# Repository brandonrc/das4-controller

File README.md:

# das4-controller

An open-source replacement controller board for the **Das Keyboard 4 Professional**:
same outline, same holes, same connectors, but with an **RP2350B** you can flash
with your own firmware (pico-sdk today, KMK/CircuitPython, QMK once it supports the RP2350B). It keeps the two USB-A ports (as a USB 2.0
hub), the volume knob, the NUM/CAPS/SCROLL LEDs (now RGB, any colour) and the five buttons. Every
button gets its own GPIO, so you can make them do whatever you like.

> **Status: ready to order after a final 1:1 fit print.** Routed, DRC clean (0 unconnected, 0 real
> violations), with independent circuit and layout reviews, a check against Raspberry Pi's RP2350
> design guide, and a firmware build for this pinout. See [docs/plan.md](docs/plan.md).

| Top | Bottom |
|---|---|
|  |  |

## Docs

- [Plan and status](docs/plan.md): what's done, next steps, bring-up and firmware plan
- [Design notes](docs/design.md): architecture, circuit blocks, GPIO map, ordering, open questions
- [Bill of materials](docs/bom.md): every part with its LCSC number and live JLCPCB stock
- [Measurements](docs/measurements.md): every dimension, where it came from and how sure we are
- [Fit-check PDF](docs/fit-check-1to1.pdf): print at 100% and lay the original board on it
- Reviews: [circuit](docs/review-2026-09-25.md), [layout 1](docs/review-layout-2026-09-25.md),
  [layout 2](docs/review-layout-2-2026-09-25.md), [RPi design guide](docs/rpi-guide-check-2026-09-26.md),
  [firmware](docs/firmware-check-2026-09-26.md)
- [AGENTS.md](AGENTS.md): how the pipeline works and what to watch out for (for AI agents and humans)

## Layout

```
hardware/
  circuit/das4.py                          the circuit (SKiDL)
  das4-controller.net                      netlist generated from it
  das4-controller.kicad_pro / .kicad_pcb   KiCad 10 project (board generated from the netlist)
  lib/jlc.*                                JLCPCB part symbols, footprints and 3D models (easyeda2kicad)
  lib/das4.pretty                          our own footprints (J4 flex solder pads)
  scripts/gen_board.py                     outline, measured positions, placement, silkscreen
  scripts/critical.py                      hand-drawn critical nets + keep-outs (RP2350 regulator, USB pair, crystal...)
  scripts/route.py, route_best.py          autorouting (Freerouting) + cleanup + GND stitching, best of 6 runs
  scripts/pretest.py, check_layout.py      pre-route DRC of the hand layout; post-route checks
  scripts/jlc_fab.py                       JLCPCB gerber zip, BOM and CPL
  scripts/jlc.py                           search JLCPCB's parts library (no login)
  scripts/bom.py                           docs/bom.md with live stock
docs/                                      notes, plan, reviews, renders, fit-check print
firmware/bringup/                          pico-sdk + TinyUSB bring-up firmware for this pinout
```

## Building

The tools come from the KiBot/KiCad container
[`ghcr.io/inti-cmnb/kicad10_auto_full`](https://github.com/INTI-CMNB/kicad_auto),
which is also what CI runs.

```sh
# one-time: create the container
distrobox create --name pcb --image ghcr.io/inti-cmnb/kicad10_auto_full:1.9.1-1_k10.0.5_d13.2_b4.2.4LTS

distrobox enter pcb -- make pretest       # quick DRC of just the hand layout (run before routing)
distrobox enter pcb -- make board route   # circuit -> netlist -> placed board -> autorouted (~25 min)
distrobox enter pcb -- make check         # post-route checks DRC can't do
distrobox enter pcb -- make docs drc fab  # renders, fit-check PDF, DRC, JLCPCB files (don't rebuild the board)
distrobox enter pcb -- make bom      # refresh docs/bom.md with live JLCPCB stock
```

Or use Docker directly:
`docker run --rm -v $PWD:/w -w /w ghcr.io/inti-cmnb/kicad10_auto_full:1.9.1-1_k10.0.5_d13.2_b4.2.4LTS make`.

Open `hardware/das4-controller.kicad_pro` in KiCad 10 to look around.

**Note:** the board file is *generated*: `make board` rebuilds it (unrouted)
from the circuit and `gen_board.py`, and `make route` routes it. Edit those,
not the .kicad_pcb, or your changes get overwritten.

## Ordering (JLCPCB)

```sh
distrobox enter pcb -- make fab     # -> build/jlcpcb/: gerber zip, bom.csv, cpl.csv
```

1. On jlcpcb.com upload the gerber zip. Pick **4 layers**, 1.6 mm, and the **JLC04161H-7628** stackup with impedance control.
2. Enable **PCB Assembly** (top side), upload `bom.csv` and `cpl.csv`, and check the placement preview:
   rotations, and L1's white dot on the +1V1 pad next to C165 (details in [docs/design.md](docs/design.md#ordering-at-jlcpcb)).
3. Order the "You solder" parts in [docs/bom.md](docs/bom.md) from LCSC (they can ship together).

`make fab` names the zip `...-UNROUTED-quote-only` if the board has no traces yet.

## License

MIT, see [LICENSE](LICENSE). Not affiliated with Das Keyboard / Metadot.

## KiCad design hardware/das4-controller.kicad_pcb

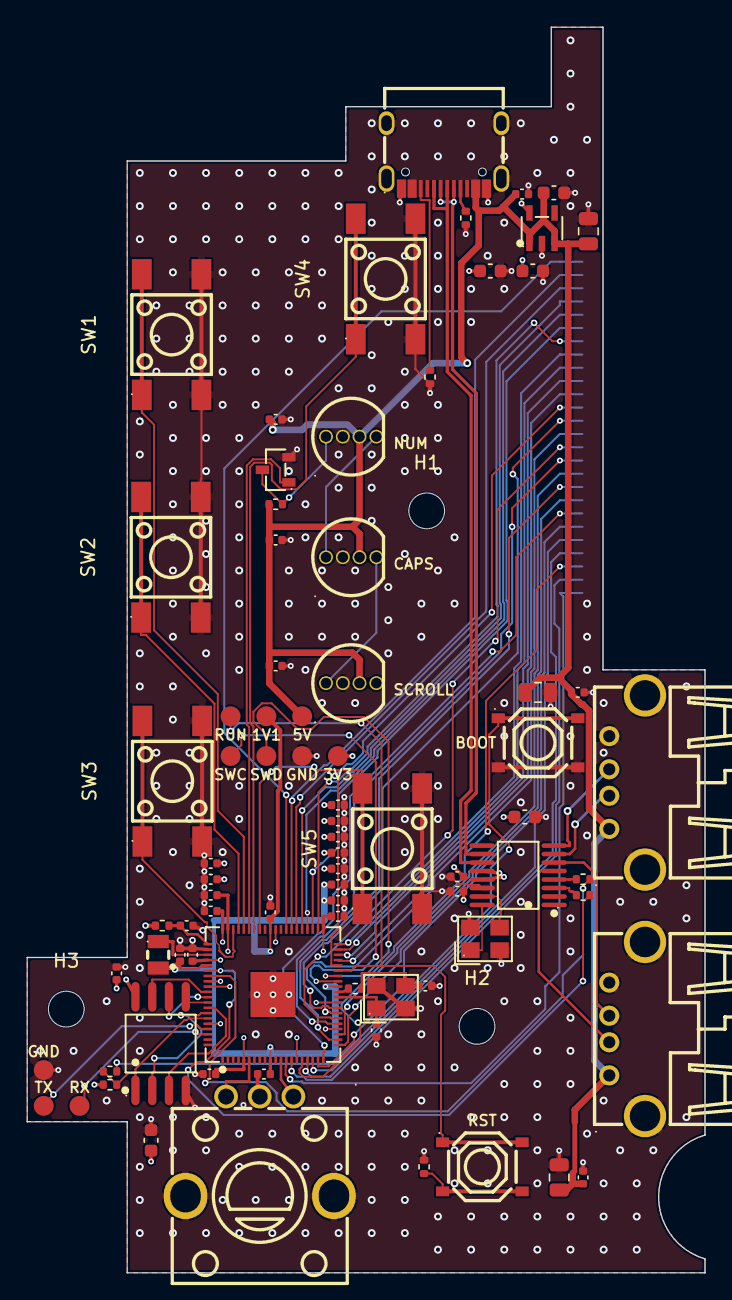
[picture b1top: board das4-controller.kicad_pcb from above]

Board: 4 copper layers, 51.1 x 94.0 mm, 83 parts (1 on the bottom side), 73 nets.

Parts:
C1, C9, C11: 22u; C_0805_2012Metric
C2, C7, C10, C12, C35, C36, C37, C105, C110, C115, C124, C129, C132, C141, C150, C151, C159, C160, C168, C169, C176, C300: 100n; C_0402_1005Metric
C3, C4, C5, C8, C190: 10u; C_0603_1608Metric
C6: 1u; C_0402_1005Metric
C161, C164, C165, C166: 4.7u; C_0402_1005Metric
C230, C231: 15p; C_0402_1005Metric
D1: NUM (RGB); LED-TH_4P-BD5.8-P1.27_WS2812D-F5-12MA-C1
D2: CAPS (RGB); LED-TH_4P-BD5.8-P1.27_WS2812D-F5-12MA-C1
D3: SCROLL (RGB); LED-TH_4P-BD5.8-P1.27_WS2812D-F5-12MA-C1
ENC1: EC12E24204A2; SW-TH_EC12E24204A2
H1, H2, H3: MountingHole_2.7mm_M2.5
J1: USB-C; USB-C_SMD-TYPE-C-31-M-12_1
J2: USB-A 1; USB-A-TH_AF-WJDG
J3: USB-A 2; USB-A-TH_AF-WJDG
J4: Key matrix flex; FPC_Solder_1x26_P1.00mm
L1: 3.3uH; IND-SMD_L2.0-W1.6_AOTA-B201610S3R3-101-T
Q1: 2N7002; SOT-23-3_L2.9-W1.3-P1.90-LS2.4-BR
R1, R2: 5.1k; R_0402_1005Metric
R10, R231, R302, R303: 1k; R_0402_1005Metric
R161: 33; R_0402_1005Metric
R266, R267: 22; R_0402_1005Metric
R301: 10k; R_0402_1005Metric
SW1: Button 1; SW-SMD_4P-L6.0-W6.0-P4.50-LS9.0_H5.0
SW2: Button 2; SW-SMD_4P-L6.0-W6.0-P4.50-LS9.0_H5.0
SW3: Button 3; SW-SMD_4P-L6.0-W6.0-P4.50-LS9.0_H5.0
SW4: Button 4; SW-SMD_4P-L6.0-W6.0-P4.50-LS9.0_H5.0
SW5: Button 5; SW-SMD_4P-L6.0-W6.0-P4.50-LS9.0_H5.0
SW6: BOOTSEL; SW-SMD_4P-L5.1-W5.1-P3.70-LS6.5-TL_H1.5
SW7: RESET; SW-SMD_4P-L5.1-W5.1-P3.70-LS6.5-TL_H1.5
TP1, TP2, TP3, TP4, TP5, TP6, TP7, TP8, TP9, TP10: TestPoint; TestPoint_Pad_D1.5mm
U1: RP2350B; QFN-80_L10.0-W10.0-P0.40-TL-EP3.4
U2: CH334R; QSOP-16_L4.9-W3.9-P0.64-LS6.0-BL
U3: W25Q128JVS; SOIC-8_L5.3-W5.3-P1.27-LS8.0-BL
U4: ME6211C33M5G-N; SOT-23-5_L3.0-W1.7-P0.95-LS2.8-BL
Y1, Y2: 12MHz; CRYSTAL-SMD_4P-L3.2-W2.5-BL

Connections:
+1V1: C110.1, C132.1, C151.1, C165.1, C166.1, L1.2, TP6.1, U1.10, U1.32, U1.51, U1.65
+3V3: C4.1, C5.1, C6.1, C7.1, C8.1, C105.1, C115.1, C124.1, C129.1, C141.1, C150.1, C159.1, C160.1, C164.1, C168.1, C169.1, C176.1, C190.1, C300.1, R161.1, R301.1, TP4.1, U1.5, U1.15, U1.24, U1.29, U1.41, U1.50, U1.59, U1.60, U1.64, U1.68, U1.69, U1.76, U2.12, U2.13, U3.8, U4.5
+5V: C1.1, C2.1, C3.1, C9.1, C10.1, C11.1, C12.1, C35.1, C36.1, C37.1, D1.2, D2.2, D3.2, J1.A4B9, J2.1, J3.1, R10.1, TP7.1, U4.1, U4.3
BTN1: SW1.1, SW1.2, U1.56
BTN2: SW2.1, SW2.2, U1.57
BTN3: SW3.1, SW3.2, U1.58
BTN4: SW4.1, SW4.2, U1.54
BTN5: SW5.1, SW5.2, U1.53
ENC_A: ENC1.A, U1.12
ENC_B: ENC1.B, U1.6
GND: C1.2, C2.2, C3.2, C4.2, C5.2, C6.2, C7.2, C8.2, C9.2, C10.2, C11.2, C12.2, C35.2, C36.2, C37.2, C105.2, C110.2, C115.2, C124.2, C129.2, C132.2, C141.2, C150.2, C151.2, C159.2, C160.2, C161.2, C164.2, C165.2, C166.2, C168.2, C169.2, C176.2, C190.2, C230.2, C231.2, C300.2, D1.3, D2.3, D3.3, ENC1.C, ENC1.D, ENC1.E, J1.1, J1.2, J1.3, J1.4, J1.A1B12, J1.B1A12, J2.4, J2.5, J3.4, J3.5, Q1.2, R1.2, R2.2, R303.2, SW1.3, SW1.4, SW2.3, SW2.4, SW3.3, SW3.4, SW4.3, SW4.4, SW5.3, SW5.4, SW6.3, SW6.4, TP3.1, TP10.1, U1.62, U1.81, U2.14, U3.4, U4.2, Y1.2, Y1.4, Y2.2, Y2.4
KM1: J4.1, U1.48
KM2: J4.2, U1.47
KM3: J4.3, U1.46
KM4: J4.4, U1.45
KM5: J4.5, U1.44
KM6: J4.6, U1.43
KM7: J4.7, U1.42
KM8: J4.8, U1.40
KM9: J4.9, U1.39
KM10: J4.10, U1.38
KM11: J4.11, U1.37
KM12: J4.12, U1.36
KM13: J4.13, U1.28
KM14: J4.14, U1.27
KM15: J4.15, U1.26
KM16: J4.16, U1.25
KM17: J4.17, U1.23
KM18: J4.18, U1.22
KM19: J4.19, U1.21
KM20: J4.20, U1.20
KM21: J4.21, U1.19
KM22: J4.22, U1.18
KM23: J4.23, U1.17
KM24: J4.24, U1.16
KM25: J4.25, U1.14
KM26: J4.26, U1.13
LED_DATA_N: Q1.1, U1.55
LED_DIN1: D1.4, Q1.3, R10.2
LED_DIN2: D1.1, D2.4
LED_DIN3: D2.1, D3.4
unnamed: J1.A5, R1.1
unnamed: J1.B5, R2.1
unnamed: U2.16, Y2.1
unnamed: U2.15, Y2.3
unnamed: R231.1, U1.31
unnamed: R267.2, U1.67
unnamed: R266.2, U1.66
unnamed: TP1.1, U1.33
unnamed: TP2.1, U1.34
unnamed: TP8.1, U1.77
unnamed: TP9.1, U1.78
QSPI_SCLK: U1.71, U3.6
QSPI_SD0: U1.72, U3.5
QSPI_SD1: U1.74, U3.2
QSPI_SD2: U1.73, U3.3
QSPI_SD3: U1.70, U3.7
QSPI_SS: R301.2, R302.1, U1.75, U3.1
RUN: SW7.1, SW7.2, TP5.1, U1.35
RUN_BTN: R303.1, SW7.3, SW7.4
USB_A1_D+: J2.3, U2.8
USB_A1_D-: J2.2, U2.7
USB_A2_D+: J3.3, U2.6
USB_A2_D-: J3.2, U2.5
USB_BOOT: R302.2, SW6.1, SW6.2
USB_MCU_D+: R267.1, U2.4
USB_MCU_D-: R266.1, U2.3
USB_UP_D+: J1.A6, J1.B6, U2.11
USB_UP_D-: J1.A7, J1.B7, U2.10
VREG_AVDD: C161.1, R161.2, U1.61
VREG_LX: L1.1, U1.63
XIN: C230.1, U1.30, Y1.1
XOUT_XTAL: C231.1, R231.2, Y1.3

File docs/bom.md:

# Bill of materials

Generated by `hardware/scripts/bom.py` from the netlist, with live JLCPCB stock (re-run it before ordering).

- **JLCPCB assembles 58 parts**: 20 unique LCSC numbers, **6 Extended** (JLCPCB charges a loading fee per Extended part type, about $3 each), about **$7.24** per board
- **You solder 11 parts** (through-hole + 6x6 buttons), about **$1.65** per board from LCSC

## Assembled by JLCPCB

| Refs | Qty | Value | Part | LCSC | Type | Stock | Unit |
|---|---|---|---|---|---|---|---|
| C1, C9, C11 | 3 | 22u | CL21A226MAQNNNE | [C45783](https://jlcpcb.com/partdetail/C45783) | Basic | 4,253,741 | $0.2199 |
| C2, C7, C10, C12, C35, C36, C37, C105, C110, C115, C124, C129, C132, C141, C150, C151, C159, C160, C168, C169, C176, C300 | 22 | 100n | CL05B104KO5NNNC | [C1525](https://jlcpcb.com/partdetail/C1525) | Basic | 24,676,480 | $0.0045 |
| C3, C4, C5, C8, C190 | 5 | 10u | CL10A106KP8NNNC | [C19702](https://jlcpcb.com/partdetail/C19702) | Basic | 11,277,781 | $0.0319 |
| C6 | 1 | 1u | CL05A105KA5NQNC | [C52923](https://jlcpcb.com/partdetail/C52923) | Basic | 6,487,369 | $0.0099 |
| C161, C164, C165, C166 | 4 | 4.7u | CL05A475MP5NRNC | [C23733](https://jlcpcb.com/partdetail/C23733) | Basic | 2,581,692 | $0.0166 |
| C230, C231 | 2 | 15p | 0402CG150J500NT | [C1548](https://jlcpcb.com/partdetail/C1548) | Basic | 1,481,668 | $0.0038 |
| J1 | 1 | USB-C | TYPE-C-31-M-12 | [C165948](https://jlcpcb.com/partdetail/C165948) | Extended | 169,220 | $0.1855 |
| L1 | 1 | 3.3uH | AOTA-B201610S3R3-101-T | [C42411119](https://jlcpcb.com/partdetail/C42411119) | Extended | 8,095 | $0.2826 |
| Q1 | 1 | 2N7002 | 2N7002 | [C8545](https://jlcpcb.com/partdetail/C8545) | Basic | 1,763,228 | $0.0178 |
| R1, R2 | 2 | 5.1k | 0402WGF5101TCE | [C25905](https://jlcpcb.com/partdetail/C25905) | Basic | 6,639,200 | $0.0024 |
| R10, R231, R302, R303 | 4 | 1k | 0402WGF1001TCE | [C11702](https://jlcpcb.com/partdetail/C11702) | Basic | 8,639,907 | $0.0018 |
| R161 | 1 | 33 | 0402WGF330JTCE | [C25105](https://jlcpcb.com/partdetail/C25105) | Basic | 2,133,942 | $0.0035 |
| R266, R267 | 2 | 22 | 0402WGF220JTCE | [C25092](https://jlcpcb.com/partdetail/C25092) | Basic | 5,223,935 | $0.0027 |
| R301 | 1 | 10k | 0402WGF1002TCE | [C25744](https://jlcpcb.com/partdetail/C25744) | Basic | 23,695,868 | $0.0034 |
| SW6, SW7 | 2 | BOOTSEL | TS-1187A-B-A-B | [C318884](https://jlcpcb.com/partdetail/C318884) | Basic | 576,645 | $0.0205 |
| U1 | 1 | RP2350B | RP2350B | [C42415655](https://jlcpcb.com/partdetail/C42415655) | Extended | 4,271 | $1.2781 |
| U2 | 1 | CH334R | CH334R | [C4154405](https://jlcpcb.com/partdetail/C4154405) | Extended | 21,525 | $0.5603 |
| U3 | 1 | W25Q128JVS | W25Q128JVSIQ | [C97521](https://jlcpcb.com/partdetail/C97521) | Basic | 59,683 | $2.5496 |
| U4 | 1 | ME6211C33M5G-N | ME6211C33M5G-N | [C82942](https://jlcpcb.com/partdetail/C82942) | Extended | 178,470 | $0.0606 |
| Y1, Y2 | 2 | 12MHz | ABM8-272-T3 | [C20625731](https://jlcpcb.com/partdetail/C20625731) | Extended | 16,592 | $0.6188 |

## You solder (order these from LCSC)

Kept out of the JLCPCB BOM to skip their Extended-part fees. All are through-hole or big SMD pads.

| Refs | Qty | Value | Part | LCSC | Type | Stock | Unit |
|---|---|---|---|---|---|---|---|
| D1, D2, D3 | 3 | NUM (RGB) | WS2812D-F5-12mA-C1 | [C4154875](https://jlcpcb.com/partdetail/C4154875) | Extended | 319 | $0.2003 |
| ENC1 | 1 | EC12E24204A2 | EC12E24204A2 | [C351238](https://jlcpcb.com/partdetail/C351238) | Extended | 1,227 | $0.8640 |
| J2, J3 | 2 | USB-A 1 | AF 90 WJDG | [C456018](https://jlcpcb.com/partdetail/C456018) | Extended | 78,935 | $0.0439 |
| SW1, SW2, SW3, SW4, SW5 | 5 | Button 1 | KH-6X6X5H-STM | [C2837531](https://jlcpcb.com/partdetail/C2837531) | Extended | 606,271 | $0.0187 |

## Not ordered

- **J4** Key matrix flex (das4:FPC_Solder_1x26_P1.00mm)
- **TP1** TestPoint (TestPoint:TestPoint_Pad_D1.5mm)
- **TP2** TestPoint (TestPoint:TestPoint_Pad_D1.5mm)
- **TP3** TestPoint (TestPoint:TestPoint_Pad_D1.5mm)
- **TP4** TestPoint (TestPoint:TestPoint_Pad_D1.5mm)
- **TP5** TestPoint (TestPoint:TestPoint_Pad_D1.5mm)
- **TP6** TestPoint (TestPoint:TestPoint_Pad_D1.5mm)
- **TP7** TestPoint (TestPoint:TestPoint_Pad_D1.5mm)

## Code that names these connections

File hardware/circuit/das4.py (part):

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# GPIO assignment. Any RP2350 GPIO can do any of these jobs, so this table is
# the only thing to change when layout wants a different pin order.
# J4 pin k -> GPIO(40 - k): pin 1 -> GPIO39 ... pin 26 -> GPIO14. That order
# follows the RP2350B's pins round the package, and J4's pins run in order
# too, so the 26 lines fan out to J4 without crossing each other. It also
# keeps them off GPIO40-47, which (unlike GPIO0-39) are not 5 V tolerant.
J4_GPIO = [40 - k for k in range(1, 27)]
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# towards the buttons.
BUTTON_GPIO = [45, 46, 47, 43, 42]     # SW1..SW5
# encoder either side of DVDD pin 10's cap, straight down to its pins
ENC_A_GPIO, ENC_B_GPIO = 13, 8
LED_DATA_GPIO = 44                     # WS2812 chain: NUM -> CAPS -> SCROLL
# UART0 debug pads: GPIO0 (TX), GPIO1 (RX). Spare: GPIO2-7, GPIO9-12, GPIO40-41

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v33 += mcu["VREG_VIN"]                          # pin 64
C("4.7u", mcu["VREG_VIN"], ref="C164")
C("10u", v33, ref="C190")                       # bulk
vreg_avdd = Net("VREG_AVDD")                    # pin 61: 33R + 4.7u RC filter
R("33", v33, vreg_avdd, ref="R161")
vreg_avdd += mcu["VREG_AVDD"]
C("4.7u", vreg_avdd, ref="C161")
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# QSPI flash, 16 MB
fl = jlc("W25Q128JVSIQTR", "U3", "C97521", "W25Q128JVS")
qspi_ss = Net("QSPI_SS")
qspi_ss += mcu["QSPI_SS"], fl[1]   # pin 1 = /CS
Net("QSPI_SCLK").connect(mcu["QSPI_SCLK"], fl["CLK"])
Net("QSPI_SD0").connect(mcu["QSPI_SD0"], fl["DI"])
Net("QSPI_SD1").connect(mcu["QSPI_SD1"], fl["DO"])
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
# --- Volume encoder (no switch; A/B with internal pull-ups, C to GND) -------
enc = hand(jlc("EC12E24204A2", "ENC1", "C351238", "EC12E24204A2"))
Net("ENC_A").connect(enc["A"], gpio(ENC_A_GPIO))
Net("ENC_B").connect(enc["B"], gpio(ENC_B_GPIO))
gnd += enc["C"], enc["D"], enc["E"]

# --- Lock LEDs: 3 x WS2812D (5 mm THT, RGB), any colour from firmware -------
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# open-drain and non-inverting.
q = jlc("2N7002", "Q1", "C8545")
din = Net("LED_DIN1")
Net("LED_DATA_N").connect(q["G"], gpio(LED_DATA_GPIO))
gnd += q["S"]
din += q["D"]
R("1k", vbus, din)
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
